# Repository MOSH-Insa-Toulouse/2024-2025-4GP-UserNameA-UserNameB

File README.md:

# 2024-2025-4GP-UserNameA-UserNameB

## Ma todo liste

- [x] Créer le dépôt
- [x] Modifier le fichier principale de la documentation du repo `README.md`
- [x] Ajout du template pour la shield UNO

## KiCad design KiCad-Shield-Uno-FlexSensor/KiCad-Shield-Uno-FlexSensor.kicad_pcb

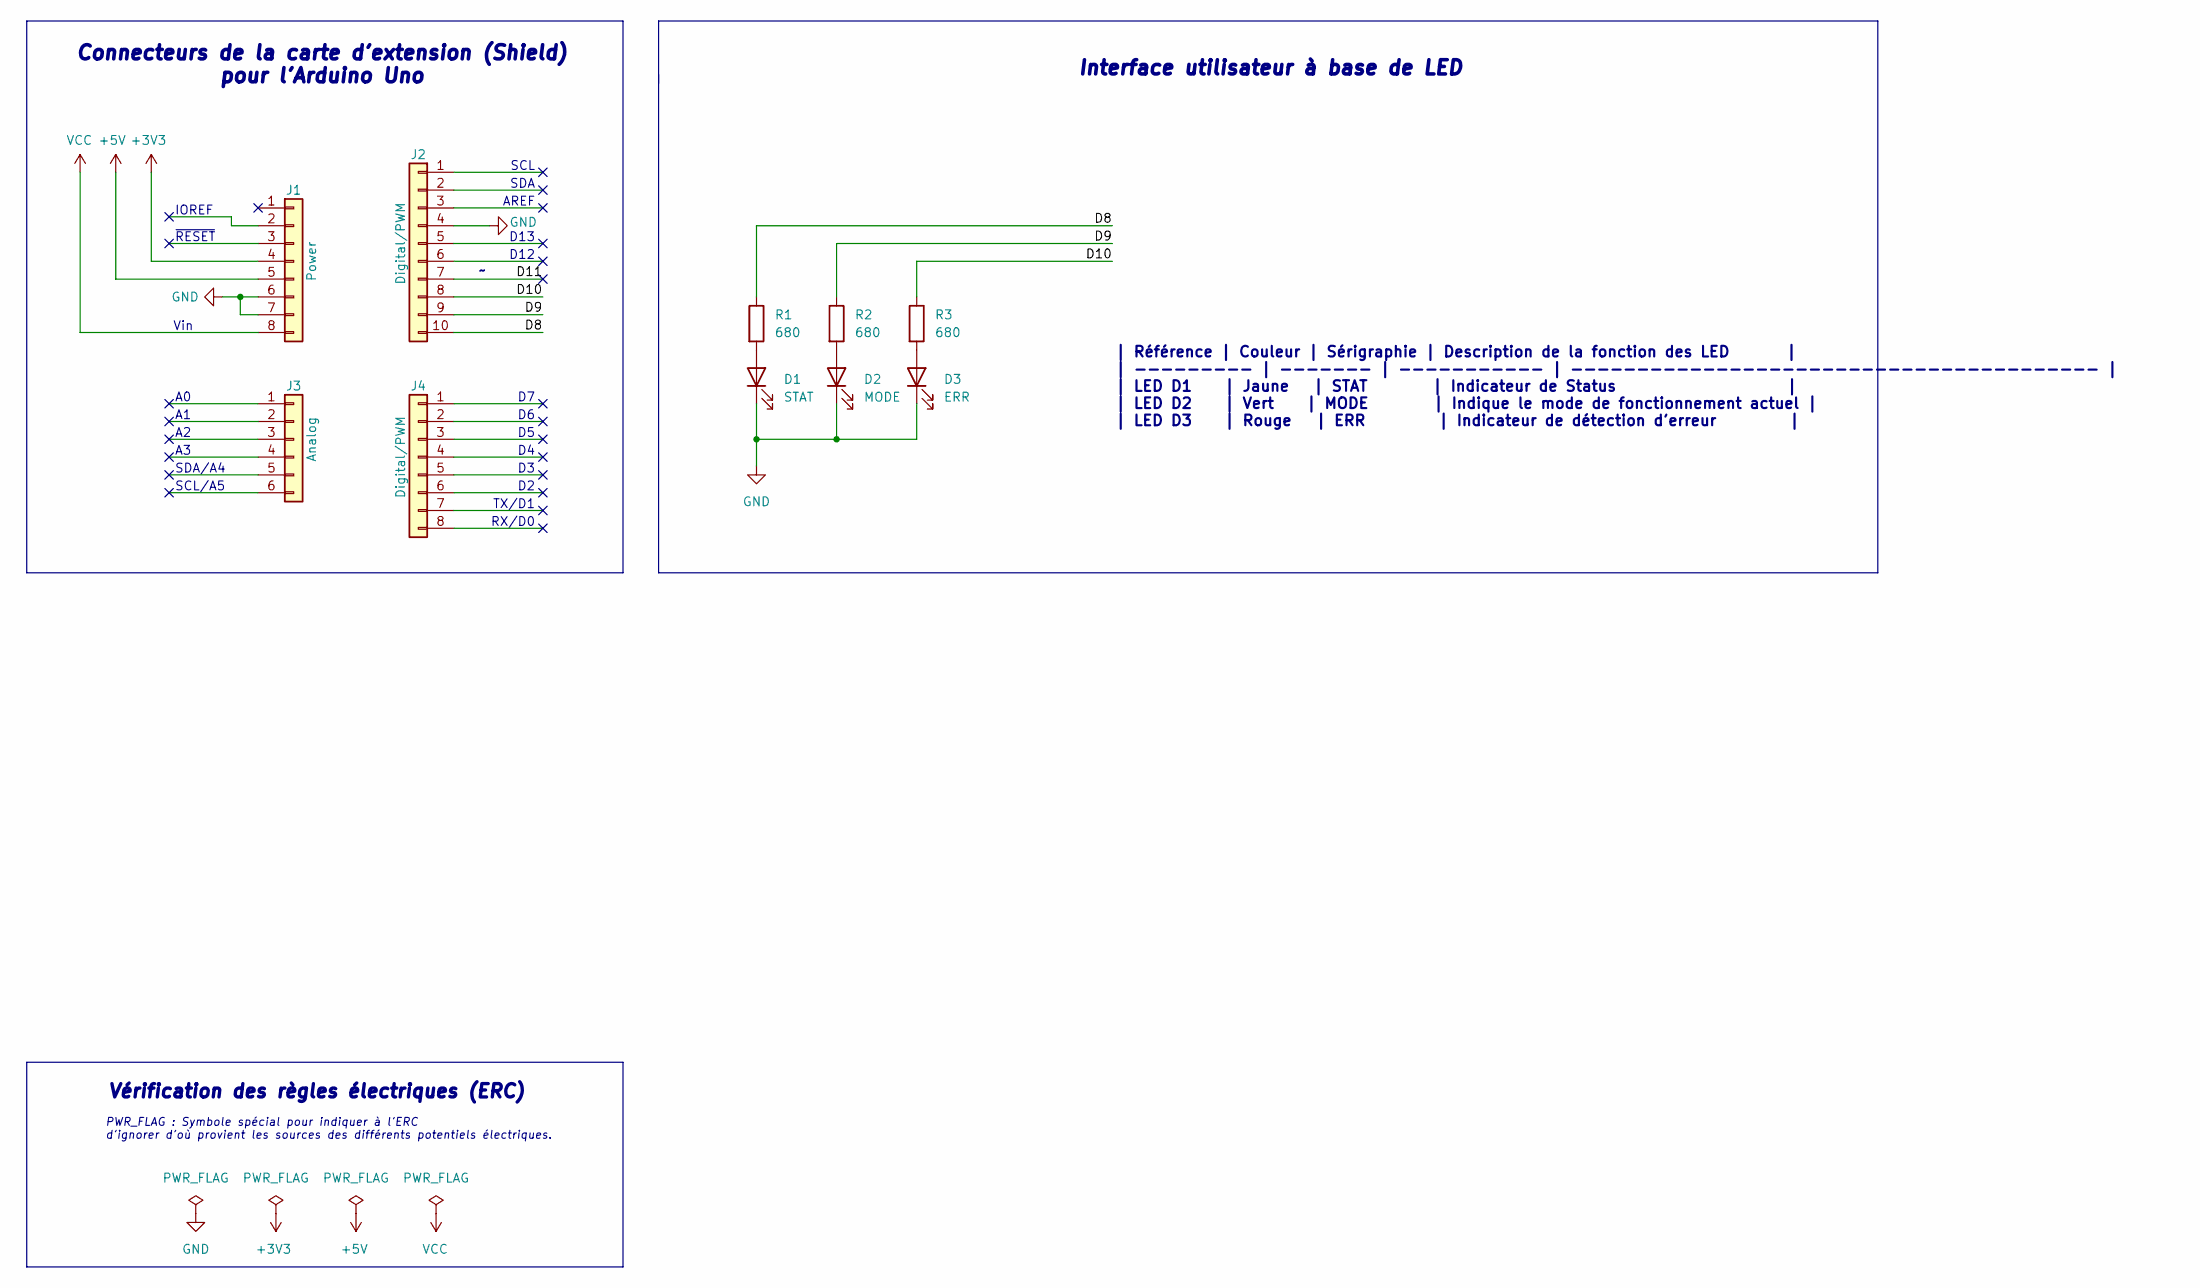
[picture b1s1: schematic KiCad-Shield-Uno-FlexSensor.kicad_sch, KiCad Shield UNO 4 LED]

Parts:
D1: STAT; LED_D5.0mm_Horizontal_O6.35mm_Z3.0mm
D2: MODE; LED_D5.0mm_Horizontal_O6.35mm_Z3.0mm
D3: ERR; LED_D5.0mm_Horizontal_O6.35mm_Z3.0mm
J1: Power; PinSocket_1x08_P2.54mm_Vertical
J2: Digital/PWM; PinSocket_1x10_P2.54mm_Vertical
J3: Analog; PinSocket_1x06_P2.54mm_Vertical
J4: Digital/PWM; PinSocket_1x08_P2.54mm_Vertical
R1, R2, R3: 680; R_Axial_DIN0207_L6.3mm_D2.5mm_P10.16mm_Horizontal

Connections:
+3V3: J1.4
+5V: J1.5
/D8: J2.10, R1.1
/D9: J2.9, R2.1
/D10: J2.8, R3.1
/D11: J2.7
GND: D1.1 (K), D2.1 (K), D3.1 (K), J1.6, J1.7, J2.4
unnamed: D1.2 (A), R1.2
unnamed: D2.2 (A), R2.2
unnamed: D3.2 (A), R3.2
VCC: J1.8

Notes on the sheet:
AREF
SDA/A4
D12
~{RESET}
RX/D0
TX/D1
D13
Vin
SDA
Vérification des règles électriques (ERC)
Interface utilisateur à base de LED
Connecteurs de la carte d'extension (Shield) pour l'Arduino Uno
| Référence | Couleur | Sérigraphie | Description de la fonction des LED | | --------- | ------- | ----------- | ---------------------------------------- | | LED D1 | Jaune | STAT | Indicateur de Status | | LED D2 | Vert | MODE | Indique le mode de fonctionnement actuel | | LED D3 | Rouge | ERR | I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
SCL/A5
SCL
IOREF
PWR_FLAG : Symbole spécial pour indiquer à l'ERC d'ignorer d'où provient les sources des différents potentiels électriques.

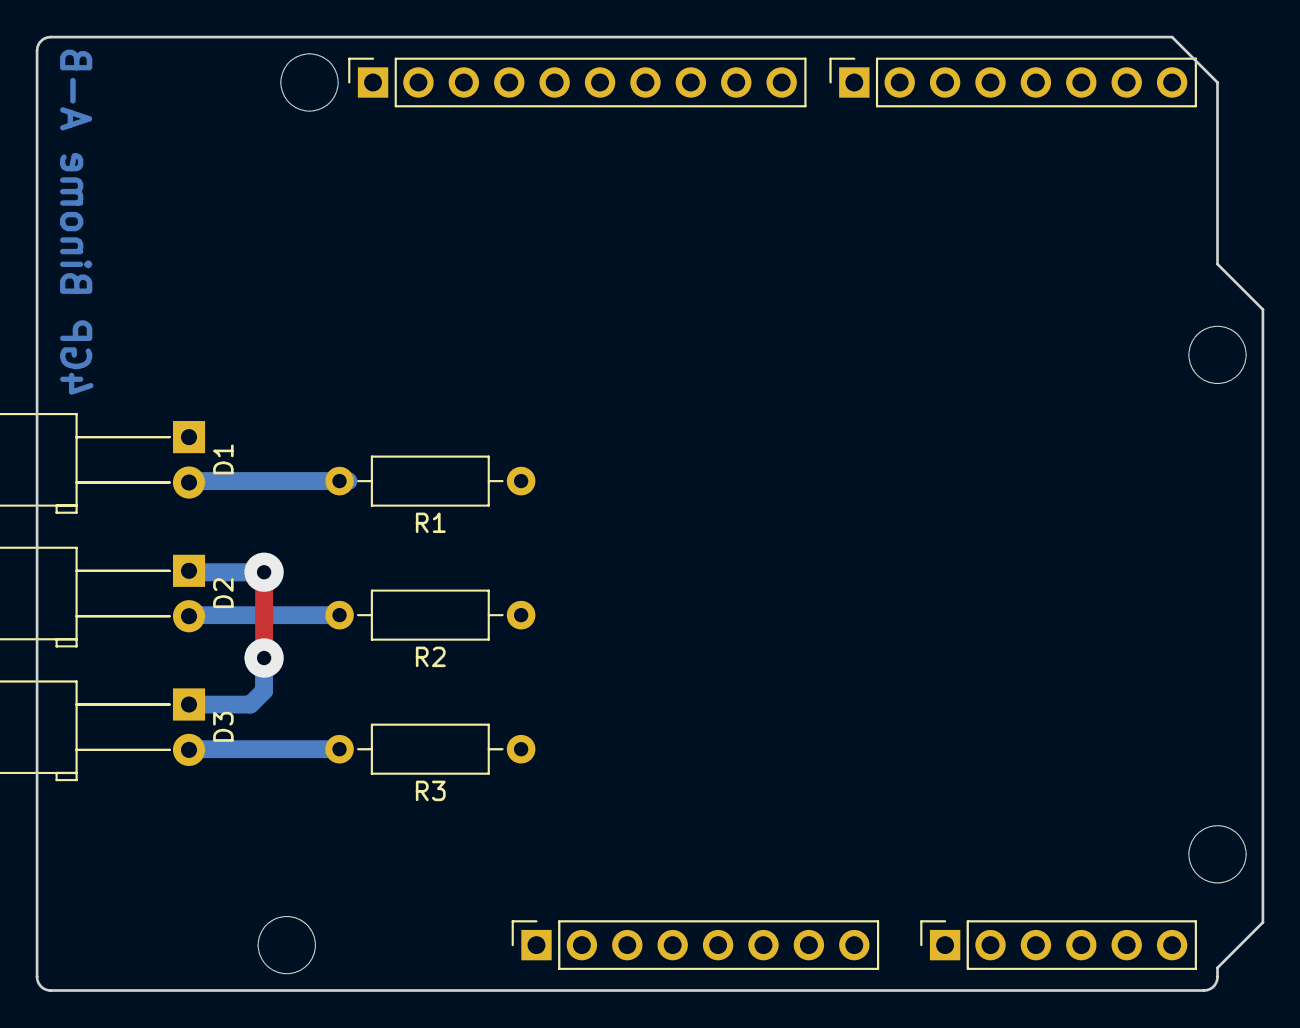
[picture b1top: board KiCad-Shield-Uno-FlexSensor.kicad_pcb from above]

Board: 2 copper layers, 68.6 x 53.3 mm, 14 parts (0 on the bottom side), 7 nets.

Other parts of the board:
MH1, MH2, MH3, MH4: MountingHole_3.2mm

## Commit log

2025-02-19 Ajout de ma todo liste
2025-02-19 Correction ligne 6
2025-02-19 Ajout du projet vide de la shield UNO
2025-03-05 Shield UNO pour démarrage projet FlexSensor
2025-03-05 Ajout des contraintes du design manager pour le routage à l'INSA
2025-03-07 Update 3D form
